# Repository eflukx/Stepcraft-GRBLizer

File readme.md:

# Stepcraft GRBLizer

A GRBL compatible controller for use as a drop-in replacement for the SC100 USB standard controller deliverd with Stepcraft CNC machines. This Arduino Uno compatible controller is wired conforming the GRL v0.9+ standard. The controller can be used with the GRBL firmware and with EstlCAM.

## Features
  - The PC is fully electrically isolated from the CNC machine (optional).
	- Device is powered via the Stepcraft machine (not from USB port) and optionally from the ISP port.
  - All inputs protected with clamping diodes and resistors.
  - Probe inputs have a 100 Ohm / 10nF low pass filter to suppress spurious triggering. (Filter values may be experimented with.)
  - 3.5mm Jack for spindle / laser / hot-end control
  - 3.5mm Jack input for 2 probes.
  - Serial interface fed out the back (TTL, not protected). For people in a hurry: CP2102 and isolator ICs can be left unpopulated.
  - Standard 6 pin ISP programming connector fed out the back  (not protected).
  - Some juper block for IO-config

Alvast een leuk plaatje:

# interactive BOM
Access the [interactive bom directly using this link](https://cdn.githubraw.com/eflukx/Stepcraft-GRBLizer/4cef8a3f/ibom/ibom.html)!
# Stepcraft 420 CNC settings with GRBLizer

Notes kindly provided by [Albin Stigö](https://github.com/ast) on getting [GRBL v1.1](https://github.com/gnea/grbl/wiki) working with the
[GRBLizer](https://github.com/eflukx/Stepcraft-GRBLizer) board.

Tested on Stepcraft 420, but probably works with most other Stepcraft types.

## Setup

* Stepcraft 420 CNC
* Stepcraft drivers with GRBLizer board
* [GRBL v1.1](https://github.com/gnea/grbl/wiki)
* [Universal-G-Code-Sender](https://github.com/winder/Universal-G-Code-Sender)

Install GRBL in the usual way. However you need to make some changes in config.h and cpu_map.h.

```c
/* cpu_map.h */

// The Stepcraft has all limits on one pin.
#define X_LIMIT_BIT    1  // Uno Digital Pin 9
#define Y_LIMIT_BIT    1  // Uno Digital Pin 9
#define Z_LIMIT_BIT    1  // Uno Digital Pin 9
```

```c
/* config.h */

// Since all limit switches end up being shared on one pin,
// we can only home one direction at a time.
#define HOMING_CYCLE_0 (1<<Z_AXIS)  // REQUIRED: First move Z to clear workspace.
#define HOMING_CYCLE_1 (1<<Y_AXIS)  // OPTIONAL: Then move X,Y at the same time.
#define HOMING_CYCLE_2 (1<<X_AXIS)  // OPTIONAL: Uncomment and add axes mask to enable

// The stop output of the Stepcraft board is inverted to what GRBL expects.
// However you simply can't swap the switch because the driver board will also
// disable the motors so nothing will move.
#define INVERT_CONTROL_PIN_MASK (1<<CONTROL_RESET_BIT) // Default disabled.
```

## GRBL settings

I haven't done a lot of fine tuning but these seems to work well enough.

```
$0 = 50				(Step pulse time, microseconds)
$1 = 100			(Step idle delay, milliseconds)
$2 = 0				(Step pulse invert, mask)
$3 = 0				(Step direction invert, mask)
$4 = 1				(Invert step enable pin, boolean)
$5 = 1				(Invert limit pins, boolean)
$6 = 0				(Invert probe pin, boolean)
$10 = 1				(Status report options, mask)
$11 = 0.010			(Junction deviation, millimeters)
$12 = 0.002			(Arc tolerance, millimeters)
$13 = 0				(Report in inches, boolean)
$20 = 0				(Soft limits enable, boolean)
$21 = 0				(Hard limits enable, boolean)
$22 = 1				(Homing cycle enable, boolean)
$23 = 1				(Homing direction invert, mask)
$24 = 120.000		(Homing locate feed rate, mm/min)
$25 = 900.000		(Homing search seek rate, mm/min)
$26 = 250			(Homing switch debounce delay, milliseconds)
$27 = 1.000			(Homing switch pull-off distance, millimeters)
$30 = 1000			(Maximum spindle speed, RPM)
$31 = 0				(Minimum spindle speed, RPM)
$32 = 0				(Laser-mode enable, boolean)
$100 = 133.333		(X-axis travel resolution, step/mm)
$101 = 133.333		(Y-axis travel resolution, step/mm)
$102 = 133.333		(Z-axis travel resolution, step/mm)
$110 = 800.000		(X-axis maximum rate, mm/min)
$111 = 800.000		(Y-axis maximum rate, mm/min)
$112 = 800.000		(Z-axis maximum rate, mm/min)
$120 = 10.000		(X-axis acceleration, mm/sec^2)
$121 = 10.000		(Y-axis acceleration, mm/sec^2)
$122 = 10.000		(Z-axis acceleration, mm/sec^2)
$130 = 300.000		(X-axis maximum travel, millimeters)
$131 = 420.000		(Y-axis maximum travel, millimeters)
$132 = 140.000		(Z-axis maximum travel, millimeters)
```

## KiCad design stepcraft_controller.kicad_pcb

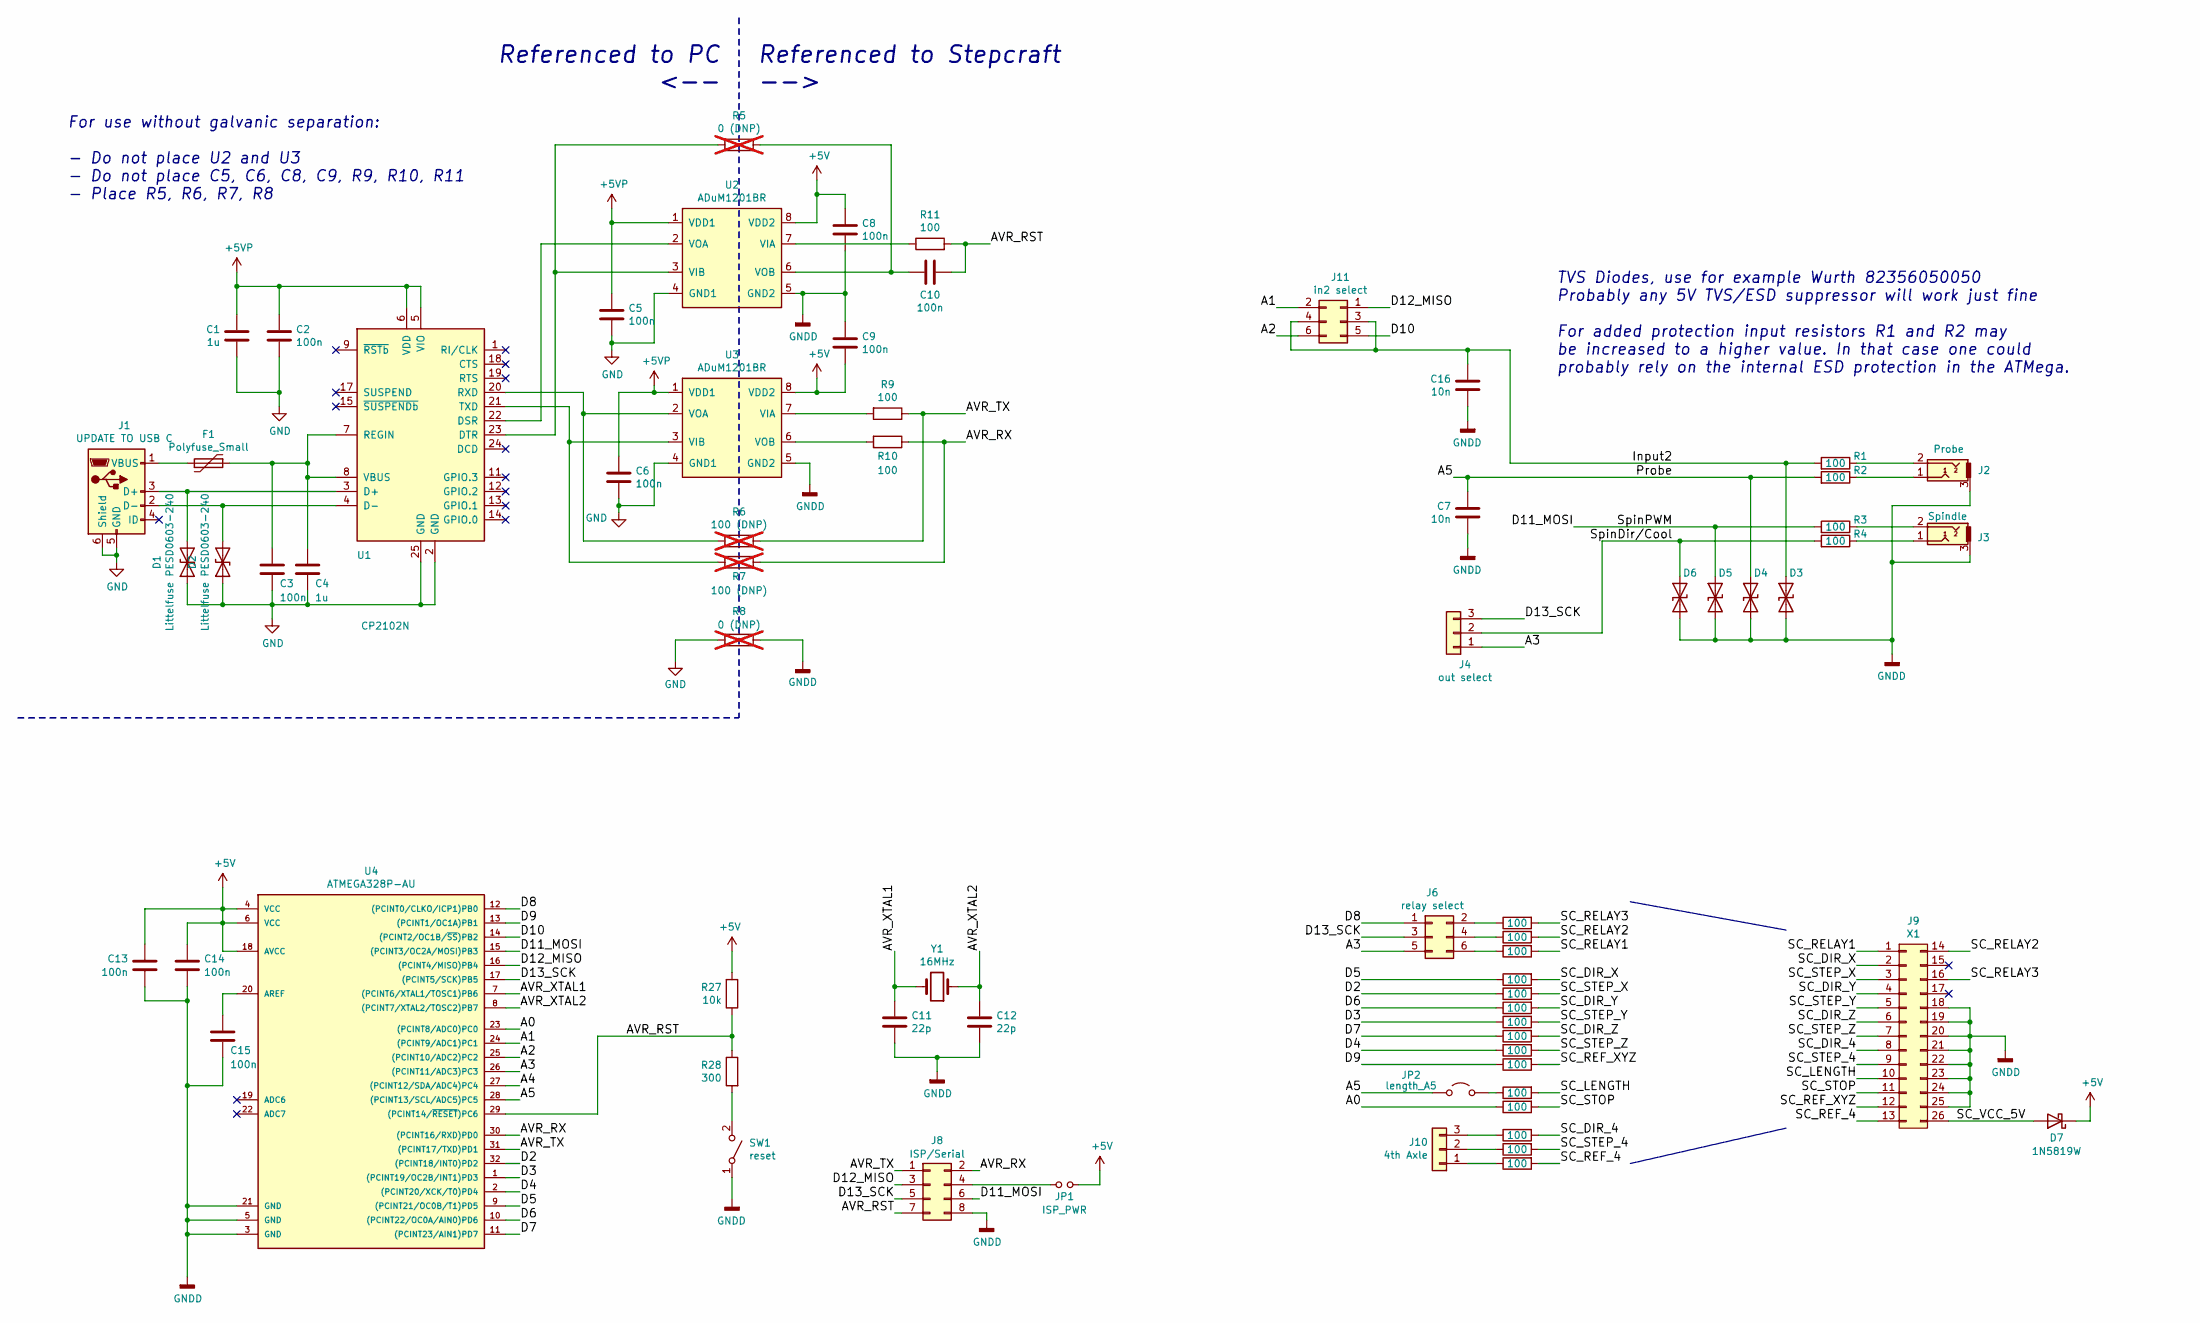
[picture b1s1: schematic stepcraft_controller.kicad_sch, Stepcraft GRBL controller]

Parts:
C1, C4: 1u; C_0805_2012Metric
C2, C3, C5, C6, C8, C9, C10, C13, C14, C15: 100n; C_0805_2012Metric
C7, C16: 10n; C_0805_2012Metric
C11, C12: 22p; C_0805_2012Metric
D1, D2, D3, D4, D5, D6: Littelfuse PESD0603-240; D_0603_1608Metric; PartNr PESD0603-240; LCSC# C2929617
D7: 1N5819W; D_SOD-123; PartNr 1N5819HW-7-F; LCSC# C82544
F1: Polyfuse_Small; Fuse_1210_3225Metric
J1: UPDATE TO USB C; USB_Micro-B_2_Holes
J2: Probe; jack_3.5_pj313d-smt; PartNr PJ-3135-B; LCSC# C319112
J3: Spindle; jack_3.5_pj313d-smt; PartNr PJ-3135-B; LCSC# C319112
J4: out select; PinHeader_1x03_P2.54mm_Vertical
J6: relay select; PinHeader_2x03_P2.54mm_Vertical
J8: ISP/Serial; PinHeader_2x04_P2.54mm_Horizontal
J9: X1; Stepcraft_SC100_Controller_Board; PartNr Generic connector 2x13pin 2.54mm
J10: 4th Axle; PinHeader_1x03_P2.54mm_Vertical
J11: in2 select; PinHeader_2x03_P2.54mm_Vertical
JP1: ISP_PWR; PinHeader_1x02_P2.54mm_Vertical
JP2: length_A5; PinHeader_1x02_P2.54mm_Vertical
R1, R2, R3, R4, R9, R10, R11, R12, R13, R14, R15, R16, R17, R18, R19, R20, R21, R22, R23, R24, R25, R26: 100; R_0805_2012Metric
R5, R8: 0 (DNP); R_0805_2012Metric; not fitted
R6, R7: 100 (DNP); R_0805_2012Metric; not fitted
R27: 10k; R_0805_2012Metric
R28: 300; R_0805_2012Metric
SW1: reset; SW_Tactile_SPST_Angled_PTS645Vx58-2LFS; PartNr PTS645VJL612LFS; LCSC# C285516
U1: CP2102N; QFN-24-1EP_4x4mm_P0.5mm_EP2.6x2.6mm; PartNr CP2102N-A02-GQFN24; LCSC# C1550551
U2, U3: ADuM1201BR; SOIC-8_3.9x4.9mm_P1.27mm; PartNr ADUM1201BRZ; LCSC# C579376
U4: ATMEGA328P-AU; TQFP-32_7x7mm_P0.8mm; PartNr ATMEGA328P-AU; LCSC# C14877
Y1: 16MHz; Crystal_SMD_HC49-SD; PartNr X49SM16MSD2SC; LCSC# C12676

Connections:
+5V: C8.1, C9.1, C13.1, C14.1, D7.1 (K), JP1.2, R27.2, U2.8 (VDD2), U3.8 (VDD2), U4.4 (VCC), U4.6 (VCC), U4.18 (AVCC)
+5VP: C1.1, C2.1, C5.1, C6.1, U1.5 (VIO), U1.6 (VDD), U2.1 (VDD1), U3.1 (VDD1)
/A0: R23.1, U4.23 ((PCINT8/ADC0)PC0)
/A1: J11.2, U4.24 ((PCINT9/ADC1)PC1)
/A2: J11.6, U4.25 ((PCINT10/ADC2)PC2)
/A3: J4.1, J6.5, U4.26 ((PCINT11/ADC3)PC3)
/A4: U4.27 ((PCINT12/SDA/ADC4)PC4)
/A5: C7.1, D4.1 (A1), JP2.1, R2.2, U4.28 ((PCINT13/SCL/ADC5)PC5)
/AVR_RST: C10.1, J8.7, R11.2, R27.1, R28.1, U4.29 ((PCINT14/~RESET)PC6)
/AVR_RX: J8.2, R7.1, R10.1, U4.30 ((PCINT16/RXD)PD0)
/AVR_TX: J8.1, R6.1, R9.1, U4.31 ((PCINT17/TXD)PD1)
/AVR_XTAL1: C11.1, U4.7 ((PCINT6/XTAL1/TOSC1)PB6), Y1.2
/AVR_XTAL2: C12.1, U4.8 ((PCINT7/XTAL2/TOSC2)PB7), Y1.1
/D2: R16.1, U4.32 ((PCINT18/INT0)PD2)
/D3: R18.1, U4.1 ((PCINT19/OC2B/INT1)PD3)
/D4: R20.1, U4.2 ((PCINT20/XCK/T0)PD4)
/D5: R15.1, U4.9 ((PCINT21/OC0B/T1)PD5)
/D6: R17.1, U4.10 ((PCINT22/OC0A/AIN0)PD6)
/D7: R19.1, U4.11 ((PCINT23/AIN1)PD7)
/D8: J6.1, U4.12 ((PCINT0/CLKO/ICP1)PB0)
/D9: R21.1, U4.13 ((PCINT1/OC1A)PB1)
/D10: J11.5, U4.14 ((PCINT2/OC1B/~SS)PB2)
/D11_MOSI: D5.1 (A1), J8.6, R3.2, U4.15 ((PCINT3/OC2A/MOSI)PB3)
/D12_MISO: J8.3, J11.1, U4.16 ((PCINT4/MISO)PB4)
/D13_SCK: J4.3, J6.3, J8.5, U4.17 ((PCINT5/SCK)PB5)
/Input2: C16.1, D3.1 (A1), J11.3, J11.4, R1.2
/SC_DIR_4: J9.8, R24.2
/SC_DIR_X: J9.2, R15.2
/SC_DIR_Y: J9.4, R17.2
/SC_DIR_Z: J9.6, R19.2
/SC_LENGTH: J9.10, R22.2
/SC_REF_4: J9.13, R26.2
/SC_REF_XYZ: J9.12, R21.2
/SC_RELAY1: J9.1, R12.2
/SC_RELAY2: J9.14 (P2), R13.2
/SC_RELAY3: J9.16, R14.2
/SC_STEP_4: J9.9, R25.2
/SC_STEP_X: J9.3, R16.2
/SC_STEP_Y: J9.5, R18.2
/SC_STEP_Z: J9.7, R20.2
/SC_STOP: J9.11, R23.2
/SC_VCC_5V: D7.2 (A), J9.26
/SpinDir/Cool: D6.1 (A1), J4.2, R4.2
GND: C1.2, C2.2, C3.2, C4.2, C5.2, C6.2, D1.1 (A1), D2.1 (A1), J1.5 (GND), J1.6 (Shield), R8.2, U1.2 (GND), U1.25 (GND), U2.4 (GND1), U3.4 (GND1)
GNDD: C7.2, C8.2, C9.2, C11.2, C12.2, C13.2, C14.2, C15.2, C16.2, D3.2 (A2), D4.2 (A2), D5.2 (A2), D6.2 (A2), J2.3, J3.3, J8.8, J9.18, J9.19, J9.20, J9.21, J9.22, J9.23, J9.24, J9.25, R8.1, SW1.1 (A), U2.5 (GND2), U3.5 (GND2), U4.3 (GND), U4.5 (GND), U4.21 (GND)
unnamed: D1.2 (A2), J1.3 (D+), U1.3 (D+)
unnamed: D2.2 (A2), J1.2 (D-), U1.4 (D-)
unnamed: F1.2, J1.1 (VBUS)
unnamed: J2.1, R2.1
unnamed: J2.2, R1.1
unnamed: J3.1, R4.1
unnamed: J3.2, R3.1
unnamed: J6.2, R14.1
unnamed: J6.4, R13.1
unnamed: J6.6, R12.1
unnamed: J8.4, JP1.1
unnamed: J10.1, R26.1
unnamed: J10.2, R25.1
unnamed: J10.3, R24.1
unnamed: JP2.2, R22.1
unnamed: R28.2, SW1.2 (B)
unnamed: U1.22 (DSR), U2.2 (VOA)
unnamed: R5.2, U1.23 (DTR), U2.3 (VIB)
unnamed: C3.1, C4.1, F1.1, U1.7 (REGIN), U1.8 (VBUS)
unnamed: R6.2, U1.20 (RXD), U3.2 (VOA)
unnamed: R7.2, U1.21 (TXD), U3.3 (VIB)
unnamed: R11.1, U2.7 (VIA)
unnamed: C10.2, R5.1, U2.6 (VOB)
unnamed: R9.2, U3.7 (VIA)
unnamed: R10.2, U3.6 (VOB)
unnamed: C15.1, U4.20 (AREF)

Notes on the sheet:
TVS Diodes, use for example Wurth 82356050050 Probably any 5V TVS/ESD suppressor will work just fine For added protection input resistors R1 and R2 may be increased to a higher value. In that case one could probably rely on the internal ESD protection in the ATMega.
Referenced to Stepcraft -->
Referenced to PC <--
For use without galvanic separation: - Do not place U2 and U3 - Do not place C5, C6, C8, C9, R9, R10, R11 - Place R5, R6, R7, R8

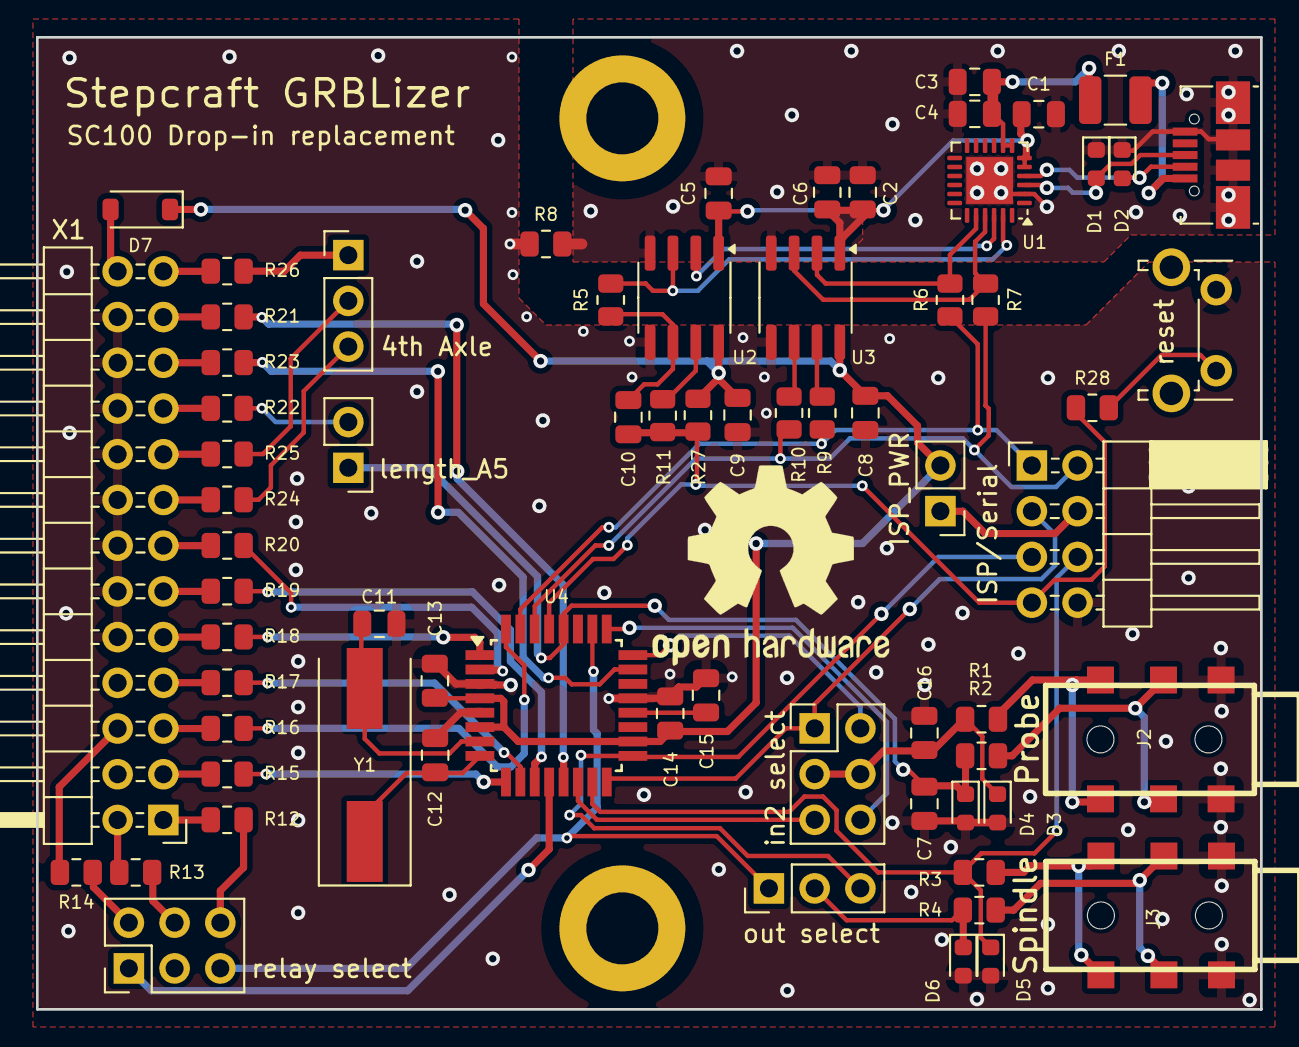
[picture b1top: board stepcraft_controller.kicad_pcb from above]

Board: 2 copper layers, 68.0 x 54.0 mm, 69 parts (0 on the bottom side), 70 nets.

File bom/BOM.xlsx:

Id | Designator | Package | Quantity | Designation | Supplier and ref | Column1 | _1
1 | U1 | QFN-24-1EP_4x4mm_Pitch0.5mm | 1 | CP2102N-A01-GQFN24
2 | J1 | conn_usb_B_micro_smd | 1 | USB
3 | J9 | Stepcraft_SC100_Controller_Board | 1 | X1
4 | C16,C7 | C_0805 | 2 | 10n
5 | JP2 | Pin_Header_Straight_1x02_Pitch2.54mm | 1 | SC_Length
6 | J10 | Pin_Header_Straight_1x03_Pitch2.54mm | 1 | 4th Axle
7 | J11 | Pin_Header_Straight_2x03_Pitch2.54mm | 1 | Input2 Select
8 | J6 | Pin_Header_Straight_2x03_Pitch2.54mm | 1 | Relay select
9 | C15,C8,C5,C9,C6,C2,C3,C10,C13,C14 | C_0805 | 10 | 100n
10 | J4 | Pin_Header_Straight_1x03_Pitch2.54mm | 1 | OutSelect
11 | R22,R20,R19,R13,R15,R16,R21,R23,R24,R25,R26,R14,R17,R18,R12,R4,R3,R2,R1,R11,R9,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 | R_0805 | 22 | 100
12 | J7 | Pin_Header_Angled_2x01_Pitch2.54mm | 1 | Serial
13 | D5,D4,D3,D2,D1,D6 | C_0603 | 6 | D_TVS
14 | U2,U3 | SOIC-8_3.9x4.9mm_Pitch1.27mm | 2 | ADuM1201BR
15 | R8,R5 | R_0805 | 2 | 0 (DNP)
16 | C1,C4 | C_0805 | 2 | 1u
17 | JP1 | Pin_Header_Straight_1x02_Pitch2.54mm | 1 | ISP_PWR
18 | C11,C12 | C_0805 | 2 | 22p
19 | Y1 | Crystal_SMD_HC49-SD | 1 | Crystal
20 | R27 | R_0805 | 1 | 10k
21 | R28 | R_0805 | 1 | 300
22 | R6,R7 | R_0805 | 2 | 100 (DNP)
23 | F1 | R_1210 | 1 | Polyfuse_Small
24 | D7 | D_SOD-123 | 1 | D_Schottky
25 | U4 | LQFP-32_7x7mm_Pitch0.8mm | 1 | ATMEGA328P-AU
26 | J8 | Pin_Header_Angled_2x03_Pitch2.54mm | 1 | ISP
27 | SW1 | TACTILE_SWITCH_VERTICAL_6MM | 1 | RST
28 | J3 | jack_3.5_pj313d-smt | 1 | Spindle
29 | J2 | jack_3.5_pj313d-smt | 1 | Probe

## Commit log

2017-09-09 Add schematics and (unrouted) board
2017-09-09 Update schematics and board, fully routed board
2017-09-09 Add readme and a nice image
2017-09-09 Update PCB routing.
2017-09-09 Add readme.md
2017-09-11 Fix net name (D13), improved routing, ground plane continuity.
2017-09-20 Change SiLabs CP2102 QFN-28 to (more common) CP2102N QFN-24
2017-09-20 Update Schematics.pdf to include changes in 855a5c1
2017-11-03 Fix Diode symbol (was reversed), input dcouple caps value, X1 caps value, minor routing improvement.
2018-07-02 Add Albin's notes on GRBL firmware on SC machines
2021-08-12 added bom and gerber
2022-11-16 Update to Kicad 5, add remarks about galvanic isolation
2022-11-16 Fix TRS jack pinning Improve some of the scuffy routing...
2022-11-16 Some more minor routing improvements
2022-11-16 Add schematics PDF for Rev 1.1 (`schematics_v1.1.pdf`)
2024-11-19 Update project to KiCad v8
    - remove all references to external footprints/symbols (close issue #3)
    - update footprints to new standard footprint
    - add components mgf partnos and LCSC part# for all non standard parts
    - shrink PCB outline by 2x0.25mm (for a better fit in machine)
    - improve routing
2024-11-21 Add interactive BOM for hand-placing parts
2024-11-29 Some silkscreen designator placement improvements

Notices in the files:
stepcraft_controller.kicad_pcb:
Rev 1.3 CC-BY
(c) 2017-24
